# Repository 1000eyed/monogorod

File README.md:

# Monogorod
This is a work in progress repository for Monogorod keyboard

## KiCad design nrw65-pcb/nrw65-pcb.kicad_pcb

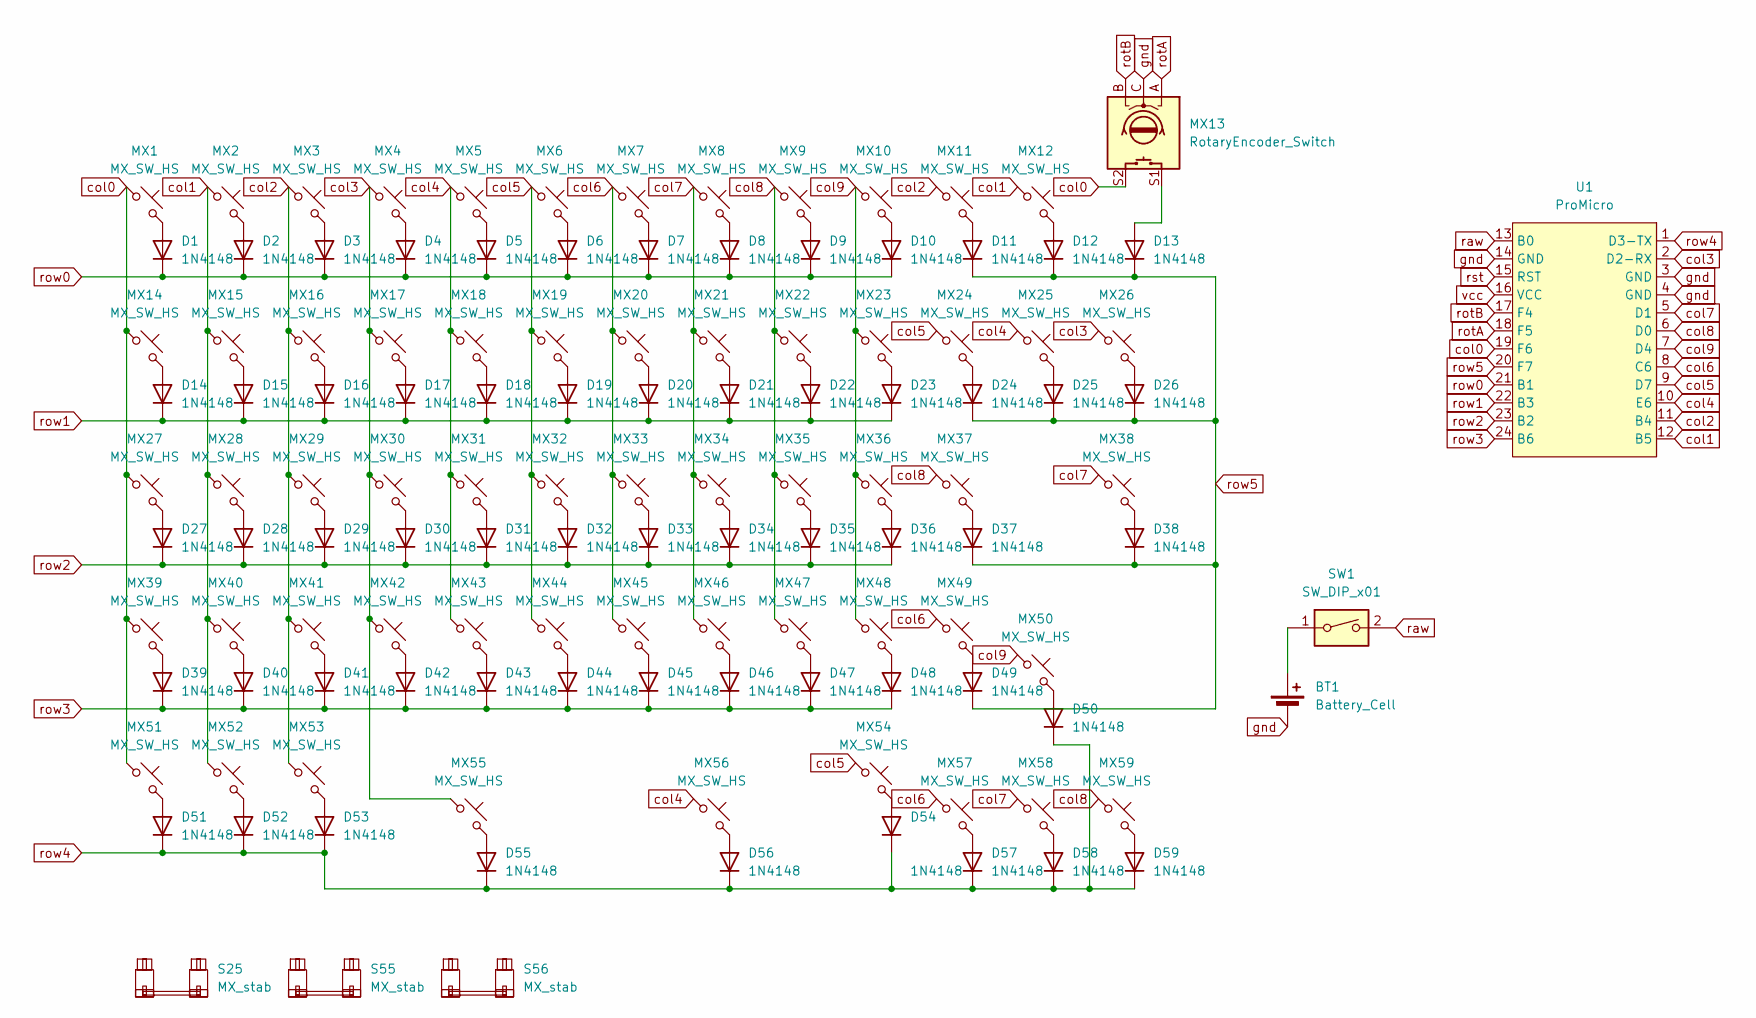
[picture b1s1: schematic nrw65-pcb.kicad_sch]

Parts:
BT1: Battery_Cell; JST_PH_S2B-PH-K_1x02_P2.00mm_Horizontal
D1, D2, D3, D4, D5, D6, D7, D8, D9, D10, D11, D12, D13, D14, D15, D16, D17, D18, D19, D20, D21, D22, D23, D24, D25, D26, D27, D28, D29, D30, D31, D32, D33, D34, D35, D36, D37, D38, D39, D40, D41, D42, D43, D44, D45, D46, D47, D48, D49, D50, D51, D52, D53, D54, D55, D56, D57, D58, D59: 1N4148; D_SOD-123 invisible designator
MX1, MX2, MX3, MX4, MX5, MX6, MX7, MX8, MX9, MX10, MX11, MX14, MX15, MX16, MX17, MX18, MX19, MX20, MX21, MX22, MX23, MX24, MX25, MX26, MX28, MX29, MX30, MX31, MX32, MX33, MX34, MX35, MX36, MX37, MX38, MX40, MX41, MX42, MX43, MX44, MX45, MX46, MX47, MX48, MX49, MX50, MX55, MX56, MX57, MX58, MX59: MX_SW_HS; SW_MX_HS_S_1u_REVERSE+KS33_HS
MX12: MX_SW_HS; SW_MX_1u+KS33
MX13: RotaryEncoder_Switch; ROT_Alps_EC11E-Switch_Invisible_designator
MX27, MX51, MX52, MX53, MX54: MX_SW_HS; SW_MX_HS_S_1.25u_REVERSE+KS33_HS
MX39: MX_SW_HS; SW_MX_HS_S_1.5u_REVERSE+KS33_HS
S25: MX_stab; STAB_MX_ISO
S55: MX_stab; STAB_MX_2.75u
S56: MX_stab; STAB_MX_2.25u
SW1: SW_DIP_x01; MSK-12C02
U1: ProMicro; ProMicro_USBup

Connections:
unnamed: BT1.1 (+), SW1.1
unnamed: D1.2 (A), MX1.2
unnamed: D2.2 (A), MX2.2
unnamed: D3.2 (A), MX3.2
unnamed: D4.2 (A), MX4.2
unnamed: D5.2 (A), MX5.2
unnamed: D6.2 (A), MX6.2
unnamed: D7.2 (A), MX7.2
unnamed: D8.2 (A), MX8.2
unnamed: D9.2 (A), MX9.2
unnamed: D10.2 (A), MX10.2
unnamed: D11.2 (A), MX11.2
unnamed: D12.2 (A), MX12.2
unnamed: D13.2 (A), MX13.S1
unnamed: D14.2 (A), MX14.2
unnamed: D15.2 (A), MX15.2
unnamed: D16.2 (A), MX16.2
unnamed: D17.2 (A), MX17.2
unnamed: D18.2 (A), MX18.2
unnamed: D19.2 (A), MX19.2
unnamed: D20.2 (A), MX20.2
unnamed: D21.2 (A), MX21.2
unnamed: D22.2 (A), MX22.2
unnamed: D23.2 (A), MX23.2
unnamed: D24.2 (A), MX24.2
unnamed: D25.2 (A), MX25.2
unnamed: D26.2 (A), MX26.2
unnamed: D27.2 (A), MX27.2
unnamed: D28.2 (A), MX28.2
unnamed: D29.2 (A), MX29.2
unnamed: D30.2 (A), MX30.2
unnamed: D31.2 (A), MX31.2
unnamed: D32.2 (A), MX32.2
unnamed: D33.2 (A), MX33.2
unnamed: D34.2 (A), MX34.2
unnamed: D35.2 (A), MX35.2
unnamed: D36.2 (A), MX36.2
unnamed: D37.2 (A), MX37.2
unnamed: D38.2 (A), MX38.2
unnamed: D39.2 (A), MX39.2
unnamed: D40.2 (A), MX40.2
unnamed: D41.2 (A), MX41.2
unnamed: D42.2 (A), MX42.2
unnamed: D43.2 (A), MX43.2
unnamed: D44.2 (A), MX44.2
unnamed: D45.2 (A), MX45.2
unnamed: D46.2 (A), MX46.2
unnamed: D47.2 (A), MX47.2
unnamed: D48.2 (A), MX48.2
unnamed: D49.2 (A), MX49.2
unnamed: D50.2 (A), MX50.2
unnamed: D51.2 (A), MX51.2
unnamed: D52.2 (A), MX52.2
unnamed: D53.2 (A), MX53.2
unnamed: D54.2 (A), MX54.2
unnamed: D55.2 (A), MX55.2
unnamed: D56.2 (A), MX56.2
unnamed: D57.2 (A), MX57.2
unnamed: D58.2 (A), MX58.2
unnamed: D59.2 (A), MX59.2
col0: MX1.1, MX13.S2, MX14.1, MX27.1, MX39.1, MX51.1, U1.19 (F6)
col1: MX2.1, MX12.1, MX15.1, MX28.1, MX40.1, MX52.1, U1.12 (B5)
col2: MX3.1, MX11.1, MX16.1, MX29.1, MX41.1, MX53.1, U1.11 (B4)
col3: MX4.1, MX17.1, MX26.1, MX30.1, MX42.1, MX55.1, U1.2 (D2-RX)
col4: MX5.1, MX18.1, MX25.1, MX31.1, MX43.1, MX56.1, U1.10 (E6)
col5: MX6.1, MX19.1, MX24.1, MX32.1, MX44.1, MX54.1, U1.9 (D7)
col6: MX7.1, MX20.1, MX33.1, MX45.1, MX49.1, MX57.1, U1.8 (C6)
col7: MX8.1, MX21.1, MX34.1, MX38.1, MX46.1, MX58.1, U1.5 (D1)
col8: MX9.1, MX22.1, MX35.1, MX37.1, MX47.1, MX59.1, U1.6 (D0)
col9: MX10.1, MX23.1, MX36.1, MX48.1, MX50.1, U1.7 (D4)
gnd: BT1.2 (-), MX13.C, U1.3 (GND), U1.4 (GND), U1.14 (GND)
raw: SW1.2, U1.13 (B0)
rotA: MX13.A, U1.18 (F5)
rotB: MX13.B, U1.17 (F4)
row0: D1.1 (K), D2.1 (K), D3.1 (K), D4.1 (K), D5.1 (K), D6.1 (K), D7.1 (K), D8.1 (K), D9.1 (K), D10.1 (K), U1.21 (B1)
row1: D14.1 (K), D15.1 (K), D16.1 (K), D17.1 (K), D18.1 (K), D19.1 (K), D20.1 (K), D21.1 (K), D22.1 (K), D23.1 (K), U1.22 (B3)
row2: D27.1 (K), D28.1 (K), D29.1 (K), D30.1 (K), D31.1 (K), D32.1 (K), D33.1 (K), D34.1 (K), D35.1 (K), D36.1 (K), U1.23 (B2)
row3: D39.1 (K), D40.1 (K), D41.1 (K), D42.1 (K), D43.1 (K), D44.1 (K), D45.1 (K), D46.1 (K), D47.1 (K), D48.1 (K), U1.24 (B6)
row4: D50.1 (K), D51.1 (K), D52.1 (K), D53.1 (K), D54.1 (K), D55.1 (K), D56.1 (K), D57.1 (K), D58.1 (K), D59.1 (K), U1.1 (D3-TX)
row5: D11.1 (K), D12.1 (K), D13.1 (K), D24.1 (K), D25.1 (K), D26.1 (K), D37.1 (K), D38.1 (K), D49.1 (K), U1.20 (F7)
rst: U1.15 (RST)
vcc: U1.16 (VCC)

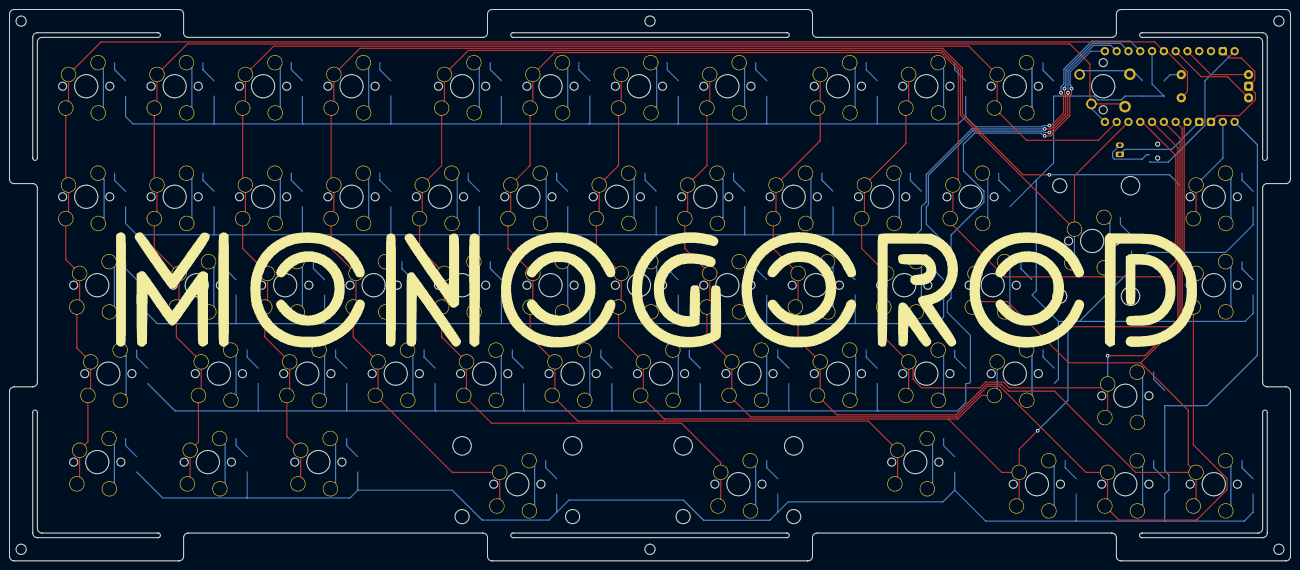
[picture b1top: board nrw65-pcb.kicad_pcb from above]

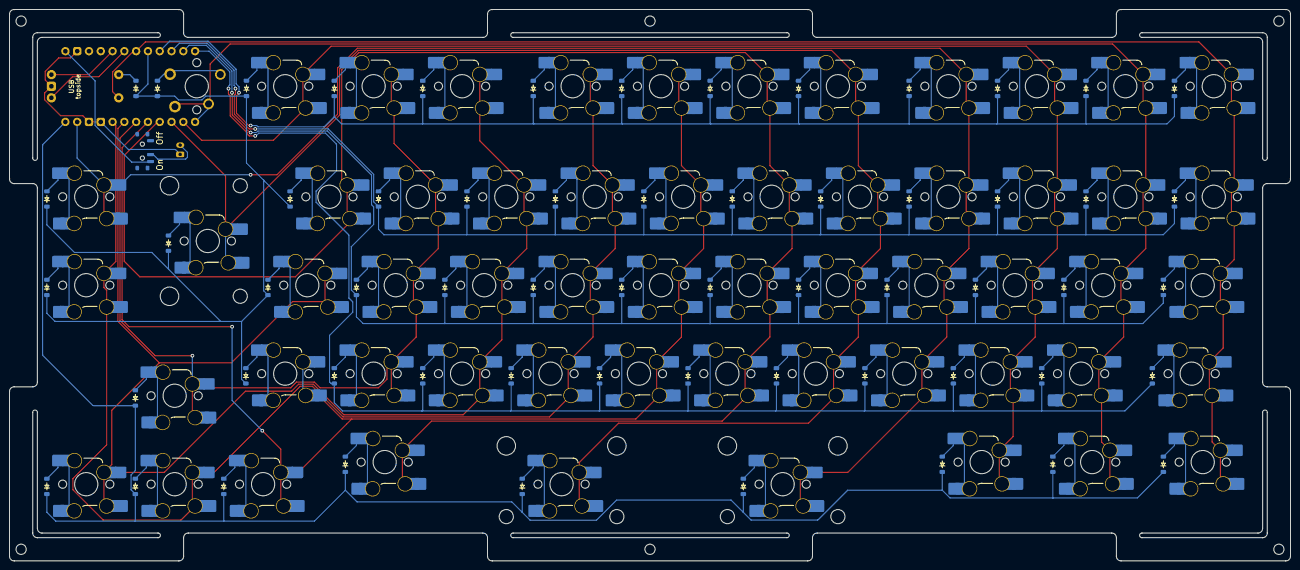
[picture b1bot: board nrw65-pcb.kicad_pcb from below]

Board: 2 copper layers, 275.9 x 118.8 mm, 124 parts (62 on the bottom side), 80 nets.

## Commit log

2023-08-02 PCB: work in progress;
2023-08-09 Work in progress
2023-08-18 add pcb and rcheme routing
2023-10-07 Work in progress: change to Pro Micro footprint, add rotary encoder, change to MX+KS33 hot swap footprints, reroute tracks.
2023-10-07 Rename project to Monorogod.
